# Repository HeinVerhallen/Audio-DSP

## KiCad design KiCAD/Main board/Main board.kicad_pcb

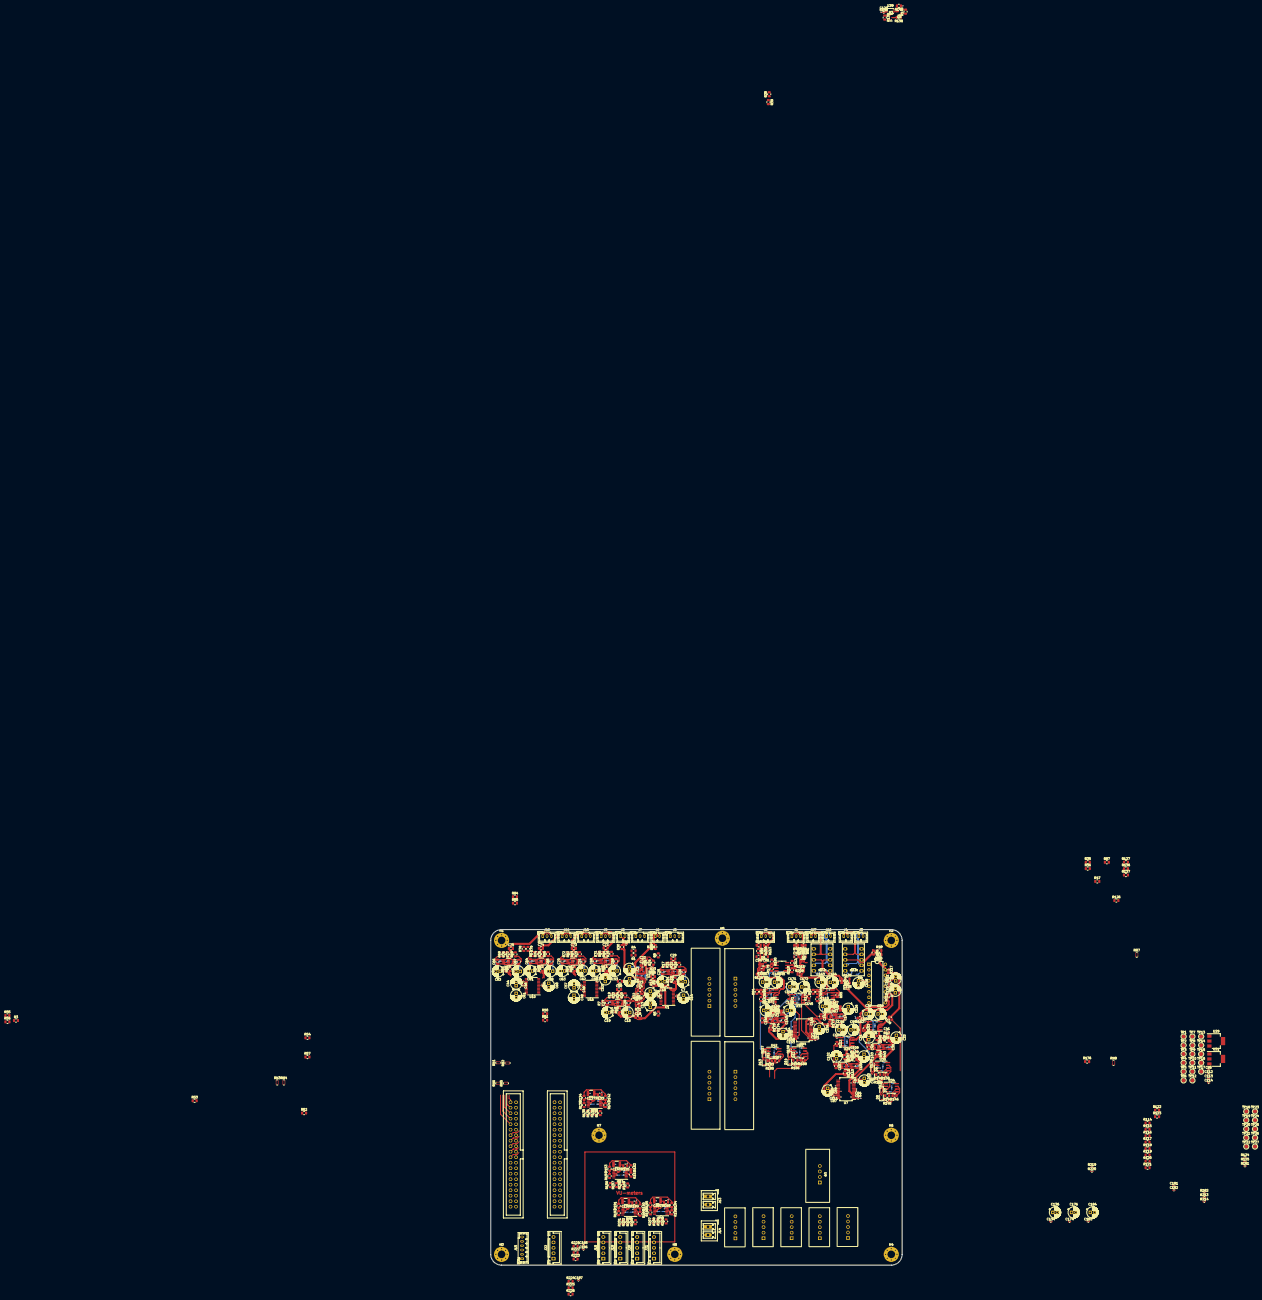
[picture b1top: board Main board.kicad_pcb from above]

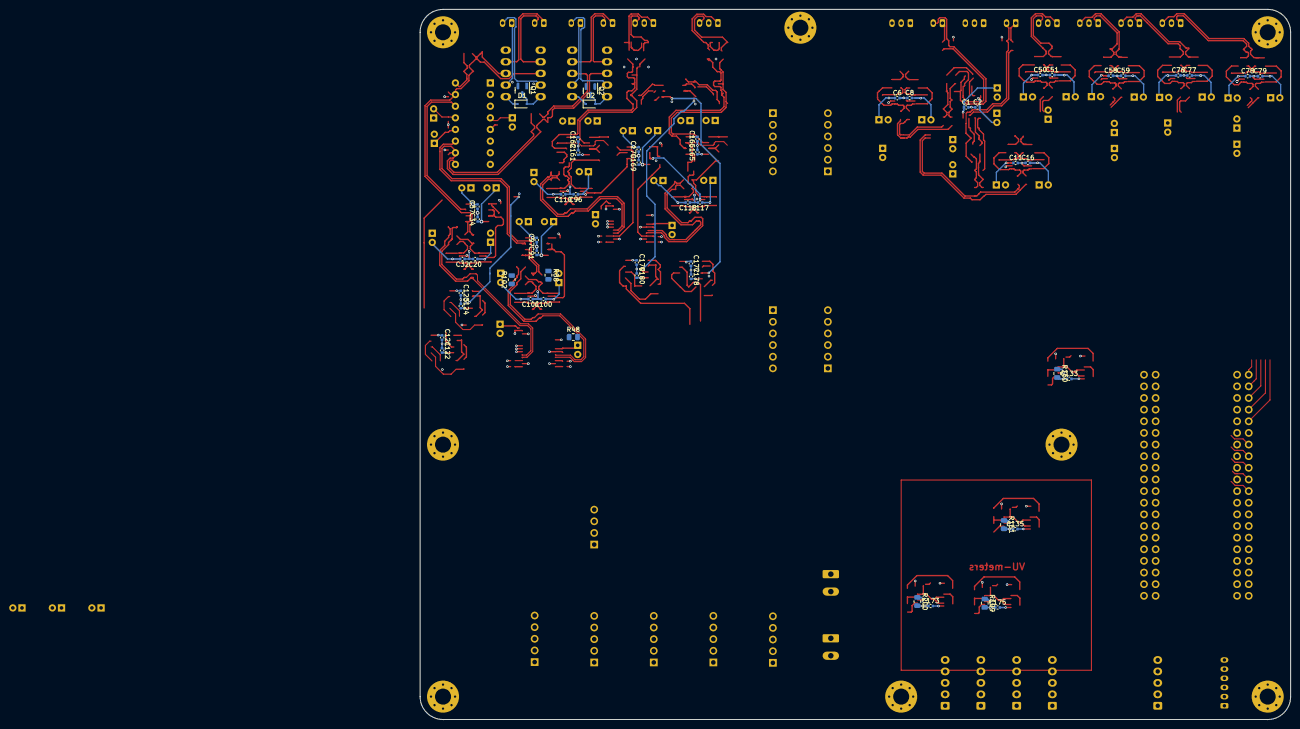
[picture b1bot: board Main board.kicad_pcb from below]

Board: 4 copper layers, 190.0 x 155.0 mm, 543 parts (55 on the bottom side), 359 nets.

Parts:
C1, C2, C5, C6, C8, C9, C11, C12, C16, C20, C32, C34, C37, C43, C45, C46, C47, C49, C50, C51, C52, C55, C58, C59, C76, C77, C78, C79, C84, C86, C87, C88, C91, C96, C97, C100, C101, C104, C109, C110, C111, C117, C118, C121, C122, C123, C124, C126, C127, C129, C130, C132, C133, C134, C135, C145, C146, C147, C148, C151, C153, C154, C155, C161, C162, C165, C166, C169, C170, C173, C174, C175, C177, C178, C179, C180, C181, C182, C183, C185, C186, C187: 100n; C_0402_1005Metric
C3, C4, C7, C10, C13, C14, C15, C19, C31, C33, C36, C38, C39, C42, C44, C48, C53, C54, C56, C57, C60, C61, C62, C63, C80, C81, C82, C83, C89, C98, C99, C102, C103, C115, C116, C119, C120, C125, C128, C131, C136, C152, C156, C163, C164, C167, C168, C171, C172, C176, C184: 22uF; CP_Radial_D5.0mm_P2.00mm
C17, C18: 4n7; C_0805_2012Metric
C21, C22, C23, C24: 1n5; C_0805_2012Metric
C25, C26, C27, C28, C64, C65, C66, C67, C68, C69, C70, C71: 680p; C_0805_2012Metric
C29, C30, C72, C73, C74, C75: 2n2; C_0805_2012Metric
C35, C40, C106, C107, C141, C142, C143, C144: 1n; C_0805_2012Metric
C41, C108, C149, C150: 2n7; C_0805_2012Metric
C85, C112, C113, C114: 1u; C_0402_1005Metric
C90, C92, C93, C94, C95, C105: 3n3; C_0805_2012Metric
C137, C140, C159, C160: 10u; C_1210_3225Metric
C138, C139, C157, C158: 47p; C_0402_1005Metric
D1, D2, D7, D8, D9, D10, D11, D12, D13, D14: 1N4148WS; D_SOD-323
D3, D4: STS321050B100; D_SOD-323
D5, D6: CPDT-12V; SOT-23
H1, H2, H3, H4, H5, H6, H7, H8: MountingHole_Pad; MountingHole_3.5mm_Pad_Via
J1, J2, J5, J7, J9, J10, J11, J12: Conn_01x03; JST_PH_B3B-PH-K_1x03_P2.00mm_Vertical
J3, J4, J6, J8, J16, J17: Conn_01x02; JST_PH_B2B-PH-K_1x02_P2.00mm_Vertical
J13, J14: Conn_01x02; PhoenixContact_MCV_1,5_2-G-3.81_1x02_P3.81mm_Vertical
J15: Conn_01x06; JST_PH_B6B-PH-K_1x06_P2.00mm_Vertical
J18, J19, J20, J21, J22: Conn_01x05; JST_XH_B5B-XH-A_1x05_P2.50mm_Vertical
K1, K2: EA2-12NU
Q1, Q2, Q3: BC847; SOT-23
Q4: BC857; SOT-23
R1, R2, R3, R4, R6, R7, R35, R36, R38, R39, R47, R48, R52, R53, R55, R56, R78, R79, R84, R85, R87, R88, R102, R114, R115, R116, R117, R118, R119, R120, R121, R122, R123, R136, R137, R176: 10R; R_0805_2012Metric
R5, R8, R50, R51, R54, R57: 4R7; R_0805_2012Metric
R9, R10, R13, R14: 10K; R_0805_2012Metric
R11, R12, R15, R16, R37, R40, R58, R59, R60, R61, R62, R63, R64, R65, R93, R94, R103, R106, R107, R112, R126, R127, R133, R134, R135, R147, R153, R154, R155, R163, R164, R165, R170, R171, R191, R192, R195, R196, R197, R198, R221, R222, R223, R224, R225, R226: 1k; R_0805_2012Metric
R17, R18, R19, R20, R66, R67, R68, R69, R70, R71, R72, R73: 4k7; R_0805_2012Metric
R21, R22, R23, R24: 820; R_0805_2012Metric
R25, R26, R27, R28: 4k3; R_0805_2012Metric
R29, R30: 22; R_0805_2012Metric
R31, R32, R33, R34, R43, R44, R74, R75, R76, R77, R80, R81, R82, R83, R110, R111, R172, R173, R174, R175: 39; R_0805_2012Metric
R41, R42, R108, R109: 2k7; R_0805_2012Metric
R45, R46, R86, R89, R90, R104: 47k; R_0805_2012Metric
R49, R91, R99, R101, R105, R113: 220; R_0805_2012Metric
R92, R100: 2M2; R_0805_2012Metric
R95, R96, R97, R98: 0; R_0805_2012Metric
R124, R125, R181, R182, R213, R214, R215, R216, R217, R218: 0R; R_0402_1005Metric
R128, R162: 100k; R_0805_2012Metric
R129, R130, R131, R132, R156, R157, R158, R159, R201, R202, R203, R204, R205, R206, R207, R208: 330; R_0805_2012Metric
R138, R139, R140, R141, R144, R145, R146, R148, R149, R150, R179, R180, R183, R184, R185, R186, R187, R188, R210, R212: 10k; R_0805_2012Metric
R142, R152, R190, R194: 2k; R_0805_2012Metric
R143, R151, R189, R193: 3k9; R_0805_2012Metric
R160, R161, R199, R200: 24k; R_0805_2012Metric
R166, R167, R168, R169: 270; R_0805_2012Metric
R177, R178, R209, R211: 150k; R_0805_2012Metric
R219, R220: 1k8; R_0402_1005Metric
RN1, RN2, RN3, RN4, RN5, RN6, RN7, RN8: 22R; R_Array_Convex_4x0402
TP1, TP2, TP3, TP4, TP5, TP6, TP7, TP8, TP9, TP10, TP11, TP12, TP13, TP14, TP15, TP16, TP17, TP18, TP19, TP20, TP21, TP22, TP23, TP24, TP25, TP26, TP27: TestPoint; TestPoint_Pad_D2.0mm
U1, U10, U16: PCM1789; TSSOP-24_4.4x7.8mm_P0.65mm
U2, U6, U24, U30, U32, U33: LM4562; SOIC-8_3.9x4.9mm_P1.27mm
U3, U4, U5, U11, U17, U22, U23, U25, U26, U27: OPA1632DR; VSSOP-8_3.0x3.0mm_P0.65_TP1.8x1.5
U7, U44: PCM1804; SSOP-28_5.3x10.2mm_P0.65mm
U8: DE1-SoC
U9: SEPIC_-15V_LT3579
U12, U13: LIN_REG_±5V; LIN_REG_±xxV
U14, U15: LIN_REG_±12V; LIN_REG_±xxV
U18, U28: 12V; BUCK_MAX17634C_xxV
U19: 5V; BUCK_MAX17634C_xxV
U20: 8V; BUCK_MAX17634C_xxV
U21: 15V; BUCK_MAX17634C_xxV
U29, U31: AP2111H-3.3TRG1; SOT-223
U34, U35, U42, U43, U45: TL072; SOIC-8_3.9x4.9mm_P1.27mm
U36, U37, U40, U41: LM339; TSSOP-14_4.4x5mm_P0.65mm
U38: PGA2311P; DIP-16_W7.62mm
U39: TXS0102; VSSOP-8_2.4x2.1mm_P0.5mm

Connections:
+3V3D1: C42.1, C43.2, C113.1, C130.2, C155.2, C156.1, R124.2, R125.2, R181.2, R182.2, R213.2, R214.2, TP2.1, U7.6 (FMT0), U7.14 (VDD), U7.19 (~RST), U29.2 (VOUT), U39.3 (VCCA), U44.6 (FMT0), U44.14 (VDD), U44.19 (~RST)
+3V3D2: C5.1, C39.1, C44.1, C45.1, C48.1, C49.1, C114.1, R219.1, R220.1, R221.1, R224.1, R225.1, TP10.1, U1.4 (RST), U1.6 (VDD), U10.4 (RST), U10.6 (VDD), U10.24 (ADR5/ADR1/RSV), U16.4 (RST), U16.6 (VDD), U16.23 (MS/ADR0/RSV), U31.2 (VOUT)
+5VA1: R48.1, R136.1, R176.1, TP3.1, U12.4 (+5V)
+5VA2: R5.1, R8.1, R50.1, R51.1, R54.1, R57.1, TP4.1, U13.4 (+5V)
+5VD1: C85.1, C112.1, C127.2, C128.1, C129.2, C133.1, C135.1, C173.1, C175.1, J15.3, J18.1, J19.1, J20.1, J21.1, Q4.2 (E), R140.2, R160.2, R161.2, R199.2, R200.2, TP1.1, U19.1 (VOUT), U19.2 (VOUT), U29.3 (VIN), U31.3 (VIN), U36.3 (V+), U37.3 (V+), U38.1 (ZCEN), U38.4 (VD+), U38.8 (~MUTE), U39.2 (VCCB), U40.3 (V+), U41.3 (V+)
+12VA1: R35.1, R38.1, R47.1, R88.1, R114.1, R116.1, R118.1, R120.1, R122.1, TP5.1, U14.4 (+12V)
+12VA2: R1.1, R3.1, R6.1, R52.1, R55.1, R78.1, R84.1, TP6.1, U15.4 (+12V)
+12VD1: D1.1 (K), D2.1 (K), K1.1, K2.1, TP13.1, U28.1 (VOUT), U28.2 (VOUT)
+15VD1: C121.1, C123.1, C177.1, C179.1, C181.1, TP11.1, U14.6 (+VIN), U15.6 (+VIN), U21.1 (VOUT), U21.2 (VOUT), U34.8 (V+), U35.8 (V+), U42.8 (V+), U43.8 (V+), U45.8 (V+)
-5VA1: R137.1, TP15.1, TP16.1, U12.3 (-5V), U13.3 (-5V)
-12VA1: R36.2, R39.2, R87.2, R102.2, R115.2, R117.2, R119.2, R121.2, R123.2, TP7.1, U14.3 (-12V)
-12VA2: R2.2, R4.2, R7.2, R53.2, R56.2, R79.2, R85.2, TP8.1, U15.3 (-12V)
-15VD1: C122.2, C124.2, C178.2, C180.2, C182.2, TP17.1, U9.3 (VOUT), U12.1 (-VIN), U13.1 (-VIN), U14.1 (-VIN), U15.1 (-VIN), U34.4 (V-), U35.4 (V-), U42.4 (V-), U43.4 (V-), U45.4 (V-)
/ADC_CH1_2/AGND_CH1: C90.2, D3.1 (A1), K1.8, R40.1, R86.2, R217.1, U38.15 (AGNDL)
/ADC_CH1_2/AGND_CH2: C105.2, D4.1 (A1), K2.8, R104.2, R107.1, R218.1, U38.10 (AGNDR)
/ADC_CH1_2/BCK_ADC_CH1_2: RN7.6 (R3.2), U8.9(GPIO_0) (GPIO_0_D8)
/ADC_CH1_2/DATA_ADC_CH1_2: RN7.5 (R4.2), U8.13(GPIO_0) (GPIO_0_D10)
/ADC_CH1_2/INPUT_SELECTOR_RELAY_CH1: R126.2, U8.1(GPIO_0) (GPIO_0_D0)
/ADC_CH1_2/INPUT_SELECTOR_RELAY_CH2: R127.2, U8.3(GPIO_0) (GPIO_0_D2)
/ADC_CH1_2/JACK_CH1(+): J4.1, K1.4
/ADC_CH1_2/JACK_CH1(REF): J4.2, K1.7
/ADC_CH1_2/JACK_CH2(+): J17.1, K2.4
/ADC_CH1_2/JACK_CH2(REF): J17.2, K2.7
/ADC_CH1_2/LRCK_ADC_CH1_2: RN7.7 (R2.2), U8.7(GPIO_0) (GPIO_0_D6)
/ADC_CH1_2/RCA_CH1(+): J3.1, K1.2
/ADC_CH1_2/RCA_CH1(REF): J3.2, K1.9
/ADC_CH1_2/RCA_CH2(+): J16.1, K2.2
/ADC_CH1_2/RCA_CH2(REF): J16.2, K2.9
/ADC_CH1_2/SCKI_ADC_CH1_2: RN7.8 (R1.2), U8.5(GPIO_0) (GPIO_0_D4)
/ADC_CH1_2/TXS0102_SCLK_CH1_2: U8.23(GPIO_0) (GPIO_0_D20), U39.5 (A1)
/ADC_CH1_2/TXS0102_SDA_CH1_2: U8.25(GPIO_0) (GPIO_0_D22), U39.4 (A2)
/ADC_CH1_2/VU_G1_CH1: J18.2, R129.1
/ADC_CH1_2/VU_G1_CH2: J19.2, R156.1
/ADC_CH1_2/VU_G2_CH1: J18.3, R130.1
/ADC_CH1_2/VU_G2_CH2: J19.3, R157.1
/ADC_CH1_2/VU_O1_CH1: J18.4, R131.1
/ADC_CH1_2/VU_O1_CH2: J19.4, R158.1
/ADC_CH1_2/VU_R1_CH1: J18.5, R132.1
/ADC_CH1_2/VU_R1_CH2: J19.5, R159.1
/ADC_CH1_2/~TXS0102_OE_CH1_2: R139.2, U8.27(GPIO_0) (GPIO_0_D24)
/ADC_CH3_4/BCK_ADC_CH3_4: RN8.6 (R3.2), U8.19(GPIO_0) (GPIO_0_D16)
/ADC_CH3_4/DATA_ADC_CH3_4: RN8.5 (R4.2), U8.21(GPIO_0) (GPIO_0_D18)
/ADC_CH3_4/LRCK_ADC_CH3_4: RN8.7 (R2.2), U8.17(GPIO_0) (GPIO_0_D14)
/ADC_CH3_4/SCKI_ADC_CH3_4: RN8.8 (R1.2), U8.15(GPIO_0) (GPIO_0_D12)
/ADC_CH3_4/VU_G1_CH3: J20.2, R201.1
/ADC_CH3_4/VU_G1_CH4: J21.2, R205.1
/ADC_CH3_4/VU_G2_CH3: J20.3, R202.1
/ADC_CH3_4/VU_G2_CH4: J21.3, R206.1
/ADC_CH3_4/VU_O1_CH3: J20.4, R203.1
/ADC_CH3_4/VU_O1_CH4: J21.4, R207.1
/ADC_CH3_4/VU_R1_CH3: J20.5, R204.1
/ADC_CH3_4/VU_R1_CH4: J21.5, R208.1
/ADC_CH3_4/XLR_CH3(+): J1.1, R89.1, R91.1
/ADC_CH3_4/XLR_CH3(-): J1.3, R90.2, R101.1
/ADC_CH3_4/XLR_CH4(+): J2.1, R46.2, R113.1
/ADC_CH3_4/XLR_CH4(-): J2.3, R45.1, R99.1
/DAC_CH1_2/AMUTEI_DAC_CH1_2: RN2.1 (R1.1), U8.33(GPIO_1) (GPIO_1_D28)
/DAC_CH1_2/BCK_DAC_CH1_2: RN1.2 (R2.1), U8.27(GPIO_1) (GPIO_1_D24)
/DAC_CH1_2/DIN_DAC_CH1_2: RN1.3 (R3.1), U8.25(GPIO_1) (GPIO_1_D22)
/DAC_CH1_2/I2C_SCL_DAC: R219.2, RN2.3 (R3.1), RN4.3 (R3.1), RN6.3 (R3.1), U8.35(GPIO_1) (GPIO_1_D30)
/DAC_CH1_2/I2C_SDA_DAC: R220.2, RN2.2 (R2.1), RN4.2 (R2.1), RN6.2 (R2.1), U8.37(GPIO_1) (GPIO_1_D32)
/DAC_CH1_2/LRCK_DAC_CH1_2: RN1.1 (R1.1), U8.31(GPIO_1) (GPIO_1_D26)
/DAC_CH1_2/RCA_JACK_CH1(+): J6.1, R29.2
/DAC_CH1_2/RCA_JACK_CH1(REF): C22.2, J6.2, R26.2, R216.1
/DAC_CH1_2/RCA_JACK_CH2(+): J8.1, R30.2
/DAC_CH1_2/RCA_JACK_CH2(REF): C24.2, J8.2, R28.2, R215.1
/DAC_CH1_2/SCKI_DAC_CH1_2: RN1.4 (R4.1), U8.23(GPIO_1) (GPIO_1_D20)
/DAC_CH1_2/VOUT_XLR_CH1(+): C29.2, J5.1, R18.2, R32.2
/DAC_CH1_2/VOUT_XLR_CH1(-): C29.1, J5.3, R17.2, R31.2
/DAC_CH1_2/VOUT_XLR_CH2(+): C30.2, J7.1, R20.2, R34.2
/DAC_CH1_2/VOUT_XLR_CH2(-): C30.1, J7.3, R19.2, R33.2
/DAC_CH3_4/AMUTEI_DAC_CH3_4: RN4.1 (R1.1), U8.21(GPIO_1) (GPIO_1_D18)
/DAC_CH3_4/BCK_DAC_CH3_4: RN3.2 (R2.1), U8.17(GPIO_1) (GPIO_1_D14)
/DAC_CH3_4/DIN_DAC_CH3_4: RN3.3 (R3.1), U8.15(GPIO_1) (GPIO_1_D12)
/DAC_CH3_4/LRCK_DAC_CH3_4: RN3.1 (R1.1), U8.19(GPIO_1) (GPIO_1_D16)
/DAC_CH3_4/SCKI_DAC_CH3_4: RN3.4 (R4.1), U8.13(GPIO_1) (GPIO_1_D10)
/DAC_CH3_4/VOUT_XLR_CH3(+): C72.2, J9.1, R70.2, R81.2
/DAC_CH3_4/VOUT_XLR_CH3(-): C72.1, J9.3, R71.2, R80.2
/DAC_CH3_4/VOUT_XLR_CH4(+): C73.2, J10.1, R73.2, R83.2
/DAC_CH3_4/VOUT_XLR_CH4(-): C73.1, J10.3, R72.2, R82.2
/DAC_CH5_6/AMUTEI_DAC_CH5_6: RN6.1 (R1.1), U8.9(GPIO_1) (GPIO_1_D8)
/DAC_CH5_6/BCK_DAC_CH5_6: RN5.2 (R2.1), U8.5(GPIO_1) (GPIO_1_D4)
/DAC_CH5_6/DIN_DAC_CH5_6: RN5.3 (R3.1), U8.3(GPIO_1) (GPIO_1_D2)
/DAC_CH5_6/LRCK_DAC_CH5_6: RN5.1 (R1.1), U8.7(GPIO_1) (GPIO_1_D6)
/DAC_CH5_6/SCKI_DAC_CH5_6: RN5.4 (R4.1), U8.1(GPIO_1) (GPIO_1_D0)
/DAC_CH5_6/VOUT_XLR_CH5(+): C74.2, J11.1, R66.2, R75.2
/DAC_CH5_6/VOUT_XLR_CH5(-): C74.1, J11.3, R67.2, R74.2
/DAC_CH5_6/VOUT_XLR_CH6(+): C75.2, J12.1, R69.2, R77.2
/DAC_CH5_6/VOUT_XLR_CH6(-): C75.1, J12.3, R68.2, R76.2
/FPGA/ENC_A: C187.1, R226.1, U8.31(GPIO_0) (GPIO_0_D26)
/FPGA/ENC_B: C186.1, R222.1, U8.33(GPIO_0) (GPIO_0_D28)
/FPGA/ENC_SW: C185.1, R223.1, U8.35(GPIO_0) (GPIO_0_D30)
/FPGA/UI_RX: J15.6, U8.37(GPIO_0) (GPIO_0_D32)
/FPGA/UI_TX: J15.4, U8.39(GPIO_0) (GPIO_0_D34)
/POWER_SUPPLIES/DC_POWER_IN: J13.1, TP14.1, U18.5 (VIN), U19.5 (VIN), U20.5 (VIN), U21.5 (VIN), U28.5 (VIN)
GND: C1.2, C2.1, C3.2, C4.1, C5.2, C6.2, C7.2, C8.1, C9.2, C10.1, C11.2, C12.2, C13.2, C14.2, C15.2, C16.1, C19.1, C20.2, C31.2, C32.1, C33.1, C34.2, C36.2, C37.1, C38.1, C39.2, C42.2, C43.1, C44.2, C45.2, C46.2, C47.2, C48.2, C49.2, C50.2, C51.1, C52.2, C53.2, C54.1, C55.2, C56.2, C57.2, C58.2, C59.1, C60.2, C61.2, C62.2, C63.1, C76.2, C77.1, C78.2, C79.1, C80.2, C81.1, C82.2, C83.1, C84.2, C85.2, C86.2, C87.2, C88.1, C89.2, C91.2, C92.2, C93.1, C94.2, C95.1, C96.2, C97.1, C98.2, C99.1, C100.2, C101.1, C102.2, C103.1, C104.1, C109.1, C110.1, C111.2, C112.2, C113.2, C114.2, C115.2, C116.1, C117.2, C118.1, C119.2, C120.1, C121.2, C122.1, C123.2, C124.1, C125.2, C126.1, C127.1, C128.2, C129.1, C130.1, C131.1, C132.1, C133.2, C134.2, C135.2, C136.2, C137.2, C140.2, C145.1, C146.1, C147.2, C148.2, C151.2, C152.2, C153.2, C154.1, C155.1, C156.2, C159.2, C160.2, C161.2, C162.1, C163.2, C164.1, C165.2, C166.1, C167.2, C168.1, C169.2, C170.1, C171.2, C172.1, C173.2, C174.2, C175.2, C176.2, C177.2, C178.1, C179.2, C180.1, C181.2, C182.1, C183.2, C184.2, C185.2, C186.2, C187.2, H1.1, H2.1, H3.1, H4.1, H5.1, H6.1, H7.1, H8.1, J1.2, J2.2, J5.2, J7.2, J9.2, J10.2, J11.2, J12.2, J13.2, J14.2, J15.1, J22.4, J22.5, Q1.2 (E), Q2.2 (E), Q3.2 (E), R92.2, R100.2, R133.1, R135.1, R141.1, R145.1, R149.1, R154.1, R155.1, R180.1, R185.1, R186.1, R192.1, R196.1, R197.1, R198.1, R212.1, R215.2, R216.2, R217.2, R218.2, TP18.1, TP19.1, TP20.1, TP21.1, TP22.1, TP23.1, TP24.1, TP25.1, TP26.1, TP27.1, U1.7 (DGND), U1.10 (AGND1), U1.15 (AGND2), U1.20 (MODE), U1.23 (MS/ADR0/RSV), U1.24 (ADR5/ADR1/RSV), U3.2 (VOCM), U3.7 (ENABLE), U3.9 (GND), U4.2 (VOCM), U4.7 (ENABLE), U4.9 (GND), U5.7 (ENABLE), U5.9 (GND), U7.2 (AGNDL), U7.7 (FMT1), U7.8 (S/~M), U7.12 (BYPAS), U7.13 (DGND), U7.23 (AGND), U7.27 (AGNDR), U8.2(GPIO_0) (GPIO_0_D1), U8.2(GPIO_1) (GPIO_1_D1), U8.4(GPIO_0) (GPIO_0_D3), U8.4(GPIO_1) (GPIO_1_D3), U8.6(GPIO_0) (GPIO_0_D5), U8.6(GPIO_1) (GPIO_1_D5), U8.8(GPIO_0) (GPIO_0_D7), U8.8(GPIO_1) (GPIO_1_D7), U8.10(GPIO_0) (GPIO_0_D9), U8.10(GPIO_1) (GPIO_1_D9), U8.12(GPIO_0) (GND), U8.12(GPIO_1) (GND), U8.14(GPIO_0) (GPIO_0_D11), U8.14(GPIO_1) (GPIO_1_D11), U8.16(GPIO_0) (GPIO_0_D13), U8.16(GPIO_1) (GPIO_1_D13), U8.18(GPIO_0) (GPIO_0_D15), U8.18(GPIO_1) (GPIO_1_D15), U8.20(GPIO_0) (GPIO_0_D17), U8.20(GPIO_1) (GPIO_1_D17), U8.22(GPIO_0) (GPIO_0_D19), U8.22(GPIO_1) (GPIO_1_D19), U8.24(GPIO_0) (GPIO_0_D21), U8.24(GPIO_1) (GPIO_1_D21), U8.26(GPIO_0) (GPIO_0_D23), U8.26(GPIO_1) (GPIO_1_D23), U8.28(GPIO_0) (GPIO_0_D25), U8.28(GPIO_1) (GPIO_1_D25), U8.30(GPIO_0) (GND), U8.30(GPIO_1) (GND), U8.32(GPIO_0) (GPIO_0_D27), U8.32(GPIO_1) (GPIO_1_D27), U8.34(GPIO_0) (GPIO_0_D29), U8.34(GPIO_1) (GPIO_1_D29), U8.36(GPIO_0) (GPIO_0_D31), U8.36(GPIO_1) (GPIO_1_D31), U8.38(GPIO_0) (GPIO_0_D33), U8.38(GPIO_1) (GPIO_1_D33), U8.40(GPIO_0) (GPIO_0_D35), U8.40(GPIO_1) (GPIO_1_D35), U9.2 (GND), U9.4 (GND), U10.7 (DGND), U10.10 (AGND1), U10.15 (AGND2), U10.20 (MODE), U10.23 (MS/ADR0/RSV), U11.2 (VOCM), U11.7 (ENABLE), U11.9 (GND), U12.2 (GND), U12.5 (GND), U13.2 (GND)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
unnamed: C17.1, R9.1, R23.1, R25.1
unnamed: C17.2, R10.2, R24.1, R26.1
unnamed: C18.1, R13.1, R21.1, R27.1
unnamed: C18.2, R14.2, R22.1, R28.1
unnamed: C21.2, R25.2, R29.1, U2.1
unnamed: C23.2, R27.2, R30.1, U2.7
unnamed: D1.2 (A), K1.10, Q1.3 (C)
unnamed: D2.2 (A), K2.10, Q2.3 (C)
unnamed: C90.1, D3.2 (A2), R49.2, U38.16 (VINL)
unnamed: C105.1, D4.2 (A2), R105.2, U38.9 (VINR)
unnamed: C93.2, D5.1 (A1), R101.2, R211.2, U30.6 (-)
unnamed: C92.1, D5.2 (A2), R91.2, R209.2, U30.2 (-)
unnamed: C95.2, D6.1 (A1), R113.2, R177.2, U32.2 (-)
unnamed: C94.1, D6.2 (A2), R99.2, R178.2, U32.6 (-)
unnamed: C138.1, D7.2 (A), R144.2, U34.2 (-)
unnamed: C138.2, D7.1 (K), D8.2 (A), U34.1
unnamed: D8.1 (K), R145.2, U34.5 (+)
unnamed: C139.1, D9.2 (A), R148.2, U35.2 (-)
unnamed: C139.2, D9.1 (K), D10.2 (A), U35.1
unnamed: D10.1 (K), R149.2, U35.5 (+)
unnamed: C157.1, D11.2 (A), R183.2, U42.2 (-)
unnamed: C157.2, D11.1 (K), D13.2 (A), U42.1
unnamed: C158.1, D12.2 (A), R184.2, U43.2 (-)
unnamed: C158.2, D12.1 (K), D14.2 (A), U43.1
unnamed: D13.1 (K), R185.2, U42.5 (+)
unnamed: D14.1 (K), R186.2, U43.5 (+)
unnamed: J22.1, R221.2, R226.2
unnamed: J22.2, R222.2, R224.2
unnamed: J22.3, R223.2, R225.2
unnamed: K1.3, R49.1, R86.1
unnamed: K2.3, R104.1, R105.1
unnamed: Q1.1 (B), R126.1
unnamed: Q2.1 (B), R127.1
unnamed: Q3.1 (B), R139.1
unnamed: Q3.3 (C), R138.2
unnamed: Q4.1 (B), R138.1, R140.1
unnamed: Q4.3 (C), R141.2, U39.6 (OE)
unnamed: R89.2, R90.1, R92.1
unnamed: R45.2, R46.1, R100.1
unnamed: R129.2, U36.2
unnamed: R130.2, U36.1
unnamed: R131.2, U36.13
unnamed: R132.2, U36.14
unnamed: R96.2, R147.1, U30.7
unnamed: R156.2, U37.2
unnamed: R157.2, U37.1
unnamed: R158.2, U37.13
unnamed: R159.2, U37.14
unnamed: R98.2, R163.1, U32.7
unnamed: R95.2, R164.1, U30.1
unnamed: R97.2, R165.1, U32.1
unnamed: R201.2, U40.2
unnamed: R202.2, U40.1
unnamed: R203.2, U40.13
unnamed: R204.2, U40.14
unnamed: R205.2, U41.2
unnamed: R206.2, U41.1
unnamed: R207.2, U41.13
unnamed: R208.2, U41.14
unnamed: RN1.8 (R1.2), U1.1 (LRCK)
unnamed: RN1.7 (R2.2), U1.2 (BCK)
unnamed: RN1.6 (R3.2), U1.3 (DIN)
unnamed: RN1.5 (R4.2), U1.5 (SCKI)
unnamed: RN2.8 (R1.2), U1.17 (AMUTEI)
unnamed: RN2.7 (R2.2), U1.21 (MD/SDA/DEMP)
unnamed: RN2.6 (R3.2), U1.22 (MC/SCL/FMT)
unnamed: RN3.8 (R1.2), U16.1 (LRCK)
unnamed: RN3.7 (R2.2), U16.2 (BCK)
unnamed: RN3.6 (R3.2), U16.3 (DIN)
unnamed: RN3.5 (R4.2), U16.5 (SCKI)
unnamed: RN4.8 (R1.2), U16.17 (AMUTEI)
unnamed: RN4.7 (R2.2), U16.21 (MD/SDA/DEMP)
unnamed: RN4.6 (R3.2), U16.22 (MC/SCL/FMT)
unnamed: RN5.8 (R1.2), U10.1 (LRCK)
unnamed: RN5.7 (R2.2), U10.2 (BCK)
unnamed: RN5.6 (R3.2), U10.3 (DIN)
unnamed: RN5.5 (R4.2), U10.5 (SCKI)
unnamed: RN6.8 (R1.2), U10.17 (AMUTEI)
unnamed: RN6.7 (R2.2), U10.21 (MD/SDA/DEMP)
unnamed: RN6.6 (R3.2), U10.22 (MC/SCL/FMT)
unnamed: RN7.1 (R1.1), U7.18 (SCKI)
unnamed: RN7.2 (R2.1), U7.17 (LRCK/DSDBCK)
unnamed: RN7.3 (R3.1), U7.16 (BCK/DSDL)
unnamed: RN7.4 (R4.1), U7.15 (DATA/DSDR)
unnamed: RN8.1 (R1.1), U44.18 (SCKI)
unnamed: RN8.2 (R2.1), U44.17 (LRCK/DSDBCK)
unnamed: RN8.3 (R3.1), U44.16 (BCK/DSDL)
unnamed: RN8.4 (R4.1), U44.15 (DATA/DSDR)
unnamed: C9.1, C13.1, R5.2, U1.8 (VCC1)
unnamed: C12.1, C14.1, R8.2, U1.16 (VCC2)
unnamed: C134.1, C136.1, U1.9 (VCOM)
unnamed: R10.1, R11.1, U1.12 (VOUTL+)
unnamed: R9.2, R12.1, U1.11 (VOUTL-)
unnamed: R14.1, R15.1, U1.13 (VOUTR+)
unnamed: R13.2, R16.1, U1.14 (VOUTR-)
unnamed: C21.1, R23.2, U2.3 (+)
unnamed: C22.1, R24.2, U2.2 (-)
unnamed: C23.1, R21.2, U2.5 (+)
unnamed: C24.1, R22.2, U2.6 (-)
unnamed: C1.1, C3.1, R1.2, U2.8 (V+)
unnamed: C2.2, C4.2, R2.1, U2.4 (V-)
unnamed: C25.1, R11.2, R17.1, U3.8 (VIN+)
unnamed: C26.1, R12.2, R18.1, U3.1 (VIN-)
unnamed: C26.2, R32.1, U3.4 (VOUT+)
unnamed: C25.2, R31.1, U3.5 (VOUT-)
unnamed: C6.1, C7.1, R3.2, U3.3 (V+)
unnamed: C8.2, C10.2, R4.1, U3.6 (V-)
unnamed: C27.1, R15.2, R19.1, U4.8 (VIN+)
unnamed: C28.1, R16.2, R20.1, U4.1 (VIN-)
unnamed: C28.2, R34.1, U4.4 (VOUT+)
unnamed: C27.2, R33.1, U4.5 (VOUT-)
unnamed: C11.1, C15.1, R6.2, U4.3 (V+)
unnamed: C16.2, C19.2, R7.1, U4.6 (V-)
unnamed: C35.1, R37.2, R41.1, U5.8 (VIN+)
unnamed: C40.1, R40.2, R42.1, U5.1 (VIN-)
unnamed: U5.2 (VOCM), U6.6 (-), U6.7
unnamed: C40.2, R44.1, U5.4 (VOUT+)
unnamed: C35.2, R43.1, U5.5 (VOUT-)
unnamed: C20.1, C31.1, R35.2, U5.3 (V+)
unnamed: C32.2, C33.2, R36.1, U5.6 (V-)
unnamed: R37.1, U6.1, U6.2 (-)
unnamed: C104.2, R103.1, U6.5 (+)
unnamed: C34.1, C36.1, R38.2, U6.8 (V+)
unnamed: C37.2, C38.2, R39.1, U6.4 (V-)
unnamed: R124.1, U7.9 (OSR0)
unnamed: R125.1, U7.10 (OSR1)
unnamed: R181.1, U7.11 (OSR2)
unnamed: C88.2, C89.1, R48.2, U7.22 (VCC)
unnamed: C84.1, R103.2, U7.3 (VCOML)
unnamed: C111.1, R112.2, U7.26 (VCOMR)
unnamed: C41.1, R41.2, R43.2, U7.4 (VINL+)
unnamed: C41.2, R42.2, R44.2, U7.5 (VINL-)
unnamed: C108.1, R108.2, R110.2, U7.25 (VINR+)
unnamed: C108.2, R109.2, R111.2, U7.24 (VINR-)
unnamed: C86.1, U7.1 (VREFL)
unnamed: C87.1, U7.28 (VREFR)
unnamed: TP12.1, U9.1 (VIN), U18.1 (VOUT), U18.2 (VOUT)
unnamed: C46.1, C60.1, R50.2, U10.8 (VCC1)
unnamed: C47.1, C61.1, R51.2, U10.16 (VCC2)
unnamed: C183.1, C184.1, U10.9 (VCOM)
unnamed: R59.1, U10.12 (VOUTL+)
unnamed: R58.1, U10.11 (VOUTL-)
unnamed: R62.1, U10.13 (VOUTR+)
unnamed: R63.1, U10.14 (VOUTR-)
unnamed: C68.1, R60.2, R71.1, U11.8 (VIN+)
unnamed: C69.1, R61.2, R70.1, U11.1 (VIN-)
unnamed: C69.2, R81.1, U11.4 (VOUT+)
unnamed: C68.2, R80.1, U11.5 (VOUT-)
unnamed: C50.1, C53.1, R52.2, U11.3 (V+)
unnamed: C51.2, C54.2, R53.1, U11.6 (V-)
unnamed: TP9.1, U12.6 (+VIN), U13.6 (+VIN), U20.1 (VOUT), U20.2 (VOUT)
unnamed: C52.1, C56.1, R54.2, U16.8 (VCC1)
unnamed: C55.1, C57.1, R57.2, U16.16 (VCC2)
unnamed: C174.1, C176.1, U16.9 (VCOM)
unnamed: R61.1, U16.12 (VOUTL+)
unnamed: R60.1, U16.11 (VOUTL-)
unnamed: R64.1, U16.13 (VOUTR+)
unnamed: R65.1, U16.14 (VOUTR-)
unnamed: C70.1, R64.2, R72.1, U17.8 (VIN+)
unnamed: C71.1, R65.2, R73.1, U17.1 (VIN-)
unnamed: C71.2, R83.1, U17.4 (VOUT+)
unnamed: C70.2, R82.1, U17.5 (VOUT-)
unnamed: C58.1, C62.1, R55.2, U17.3 (V+)
unnamed: C59.2, C63.2, R56.1, U17.6 (V-)
unnamed: C64.1, R58.2, R67.1, U22.8 (VIN+)
unnamed: C65.1, R59.2, R66.1, U22.1 (VIN-)
unnamed: C65.2, R75.1, U22.4 (VOUT+)
unnamed: C64.2, R74.1, U22.5 (VOUT-)
unnamed: C76.1, C80.1, R78.2, U22.3 (V+)
unnamed: C77.2, C81.2, R79.1, U22.6 (V-)
unnamed: C66.1, R62.2, R68.1, U23.8 (VIN+)
unnamed: C67.1, R63.2, R69.1, U23.1 (VIN-)
unnamed: C67.2, R77.1, U23.4 (VOUT+)
unnamed: C66.2, R76.1, U23.5 (VOUT-)
unnamed: C78.1, C82.1, R84.2, U23.3 (V+)
unnamed: C79.2, C83.2, R85.1, U23.6 (V-)
unnamed: R162.1, U24.3 (+), U38.11 (VOUTR)
unnamed: R106.1, U24.1, U24.2 (-)
unnamed: C109.2, R112.1, U24.5 (+)
unnamed: U24.6 (-), U24.7, U25.2 (VOCM)
unnamed: C91.1, C98.1, R47.2, U24.8 (V+)
unnamed: C97.2, C99.2, R87.1, U24.4 (V-)
unnamed: C106.1, R106.2, R108.1, U25.8 (VIN+)
unnamed: C107.1, R107.2, R109.1, U25.1 (VIN-)
unnamed: C107.2, R111.1, U25.4 (VOUT+)
unnamed: C106.2, R110.1, U25.5 (VOUT-)
unnamed: C100.1, C102.1, R88.2, U25.3 (V+)
unnamed: C101.2, C103.2, R102.1, U25.6 (V-)
unnamed: C141.1, R164.2, R166.1, U26.8 (VIN+)
unnamed: C142.1, R147.2, R167.1, U26.1 (VIN-)
unnamed: U26.2 (VOCM), U33.1, U33.2 (-)
unnamed: C142.2, R173.1, U26.4 (VOUT+)
unnamed: C141.2, R172.1, U26.5 (VOUT-)
unnamed: C96.1, C115.1, R114.2, U26.3 (V+)
unnamed: C110.2, C116.2, R115.1, U26.6 (V-)
unnamed: C143.1, R165.2, R168.1, U27.8 (VIN+)
unnamed: C144.1, R163.2, R169.1, U27.1 (VIN-)
unnamed: U27.2 (VOCM), U33.6 (-), U33.7
unnamed: C144.2, R175.1, U27.4 (VOUT+)
unnamed: C143.2, R174.1, U27.5 (VOUT-)
unnamed: C117.1, C119.1, R116.2, U27.3 (V+)
unnamed: C118.2, C120.2, R117.1, U27.6 (V-)
unnamed: R93.1, R95.1, U30.3 (+)
unnamed: R93.2, R96.1, U30.5 (+)
unnamed: C161.1, C163.1, R118.2, U30.8 (V+)
unnamed: C162.2, C164.2, R119.1, U30.4 (V-)
unnamed: R94.1, R97.1, U32.3 (+)
unnamed: R94.2, R98.1, U32.5 (+)
unnamed: C165.1, C167.1, R120.2, U32.8 (V+)
unnamed: C166.2, C168.2, R121.1, U32.4 (V-)
unnamed: C145.2, R170.1, U33.3 (+)
unnamed: C146.2, R171.1, U33.5 (+)
unnamed: C169.1, C171.1, R122.2, U33.8 (V+)
unnamed: C170.2, C172.2, R123.1, U33.4 (V-)
unnamed: R128.1, U34.3 (+)
unnamed: R144.1, R146.2, U34.6 (-)
unnamed: R162.2, U35.3 (+)
unnamed: R148.1, R150.2, U35.6 (-)
unnamed: C137.1, R133.2, R160.1, U36.5 (+), U36.7 (+), U36.9 (+), U36.11 (+)
unnamed: R143.2, R146.1, U34.7, U36.4 (-)
unnamed: R142.2, R143.1, U36.6 (-)
unnamed: R134.2, R142.1, U36.10 (-)
unnamed: R134.1, R135.2, U36.8 (-)
unnamed: C140.1, R155.2, R161.1, U37.5 (+), U37.7 (+), U37.9 (+), U37.11 (+)
unnamed: R150.1, R151.2, U35.7, U37.4 (-)
unnamed: R151.1, R152.2, U37.6 (-)
unnamed: R152.1, R153.2, U37.10 (-)
unnamed: R153.1, R154.2, U37.8 (-)
unnamed: U38.6 (SCLK), U39.8 (B1)
unnamed: U38.3 (SDI), U39.1 (B2)
unnamed: C125.1, C126.2, R136.2, U38.12 (VA+)
unnamed: C131.2, C132.2, R137.2, U38.13 (VA-)
unnamed: R128.2, U6.3 (+), U38.14 (VOUTL)
unnamed: C159.1, R197.2, R199.1, U40.5 (+), U40.7 (+), U40.9 (+), U40.11 (+)
unnamed: R187.1, R189.2, U40.4 (-), U42.7
unnamed: R189.1, R190.2, U40.6 (-)
unnamed: R190.1, R191.2, U40.10 (-)
unnamed: R191.1, R192.2, U40.8 (-)
unnamed: C160.1, R198.2, R200.1, U41.5 (+), U41.7 (+), U41.9 (+), U41.11 (+)
unnamed: R188.1, R193.2, U41.4 (-), U43.7
unnamed: R193.1, R194.2, U41.6 (-)
unnamed: R194.1, R195.2, U41.10 (-)
unnamed: R195.1, R196.2, U41.8 (-)
unnamed: R210.1, U42.3 (+), U45.1
unnamed: R183.1, R187.2, U42.6 (-)
unnamed: R179.1, U43.3 (+), U45.7
unnamed: R184.1, R188.2, U43.6 (-)
unnamed: R182.1, U44.9 (OSR0)
unnamed: R213.1, U44.10 (OSR1)
unnamed: R214.1, U44.11 (OSR2)
unnamed: C152.1, C154.2, R176.2, U44.22 (VCC)
unnamed: C147.1, R170.2, U44.3 (VCOML)
unnamed: C148.1, R171.2, U44.26 (VCOMR)
unnamed: C149.1, R166.2, R172.2, U44.4 (VINL+)
unnamed: C149.2, R167.2, R173.2, U44.5 (VINL-)
unnamed: C150.1, R168.2, R174.2, U44.25 (VINR+)
unnamed: C150.2, R169.2, R175.2, U44.24 (VINR-)
unnamed: C151.1, U44.1 (VREFL)
unnamed: C153.1, U44.28 (VREFR)
unnamed: R211.1, R212.2, U45.3 (+)
unnamed: R209.1, R210.2, U45.2 (-)
unnamed: R178.1, R180.2, U45.5 (+)
unnamed: R177.1, R179.2, U45.6 (-)

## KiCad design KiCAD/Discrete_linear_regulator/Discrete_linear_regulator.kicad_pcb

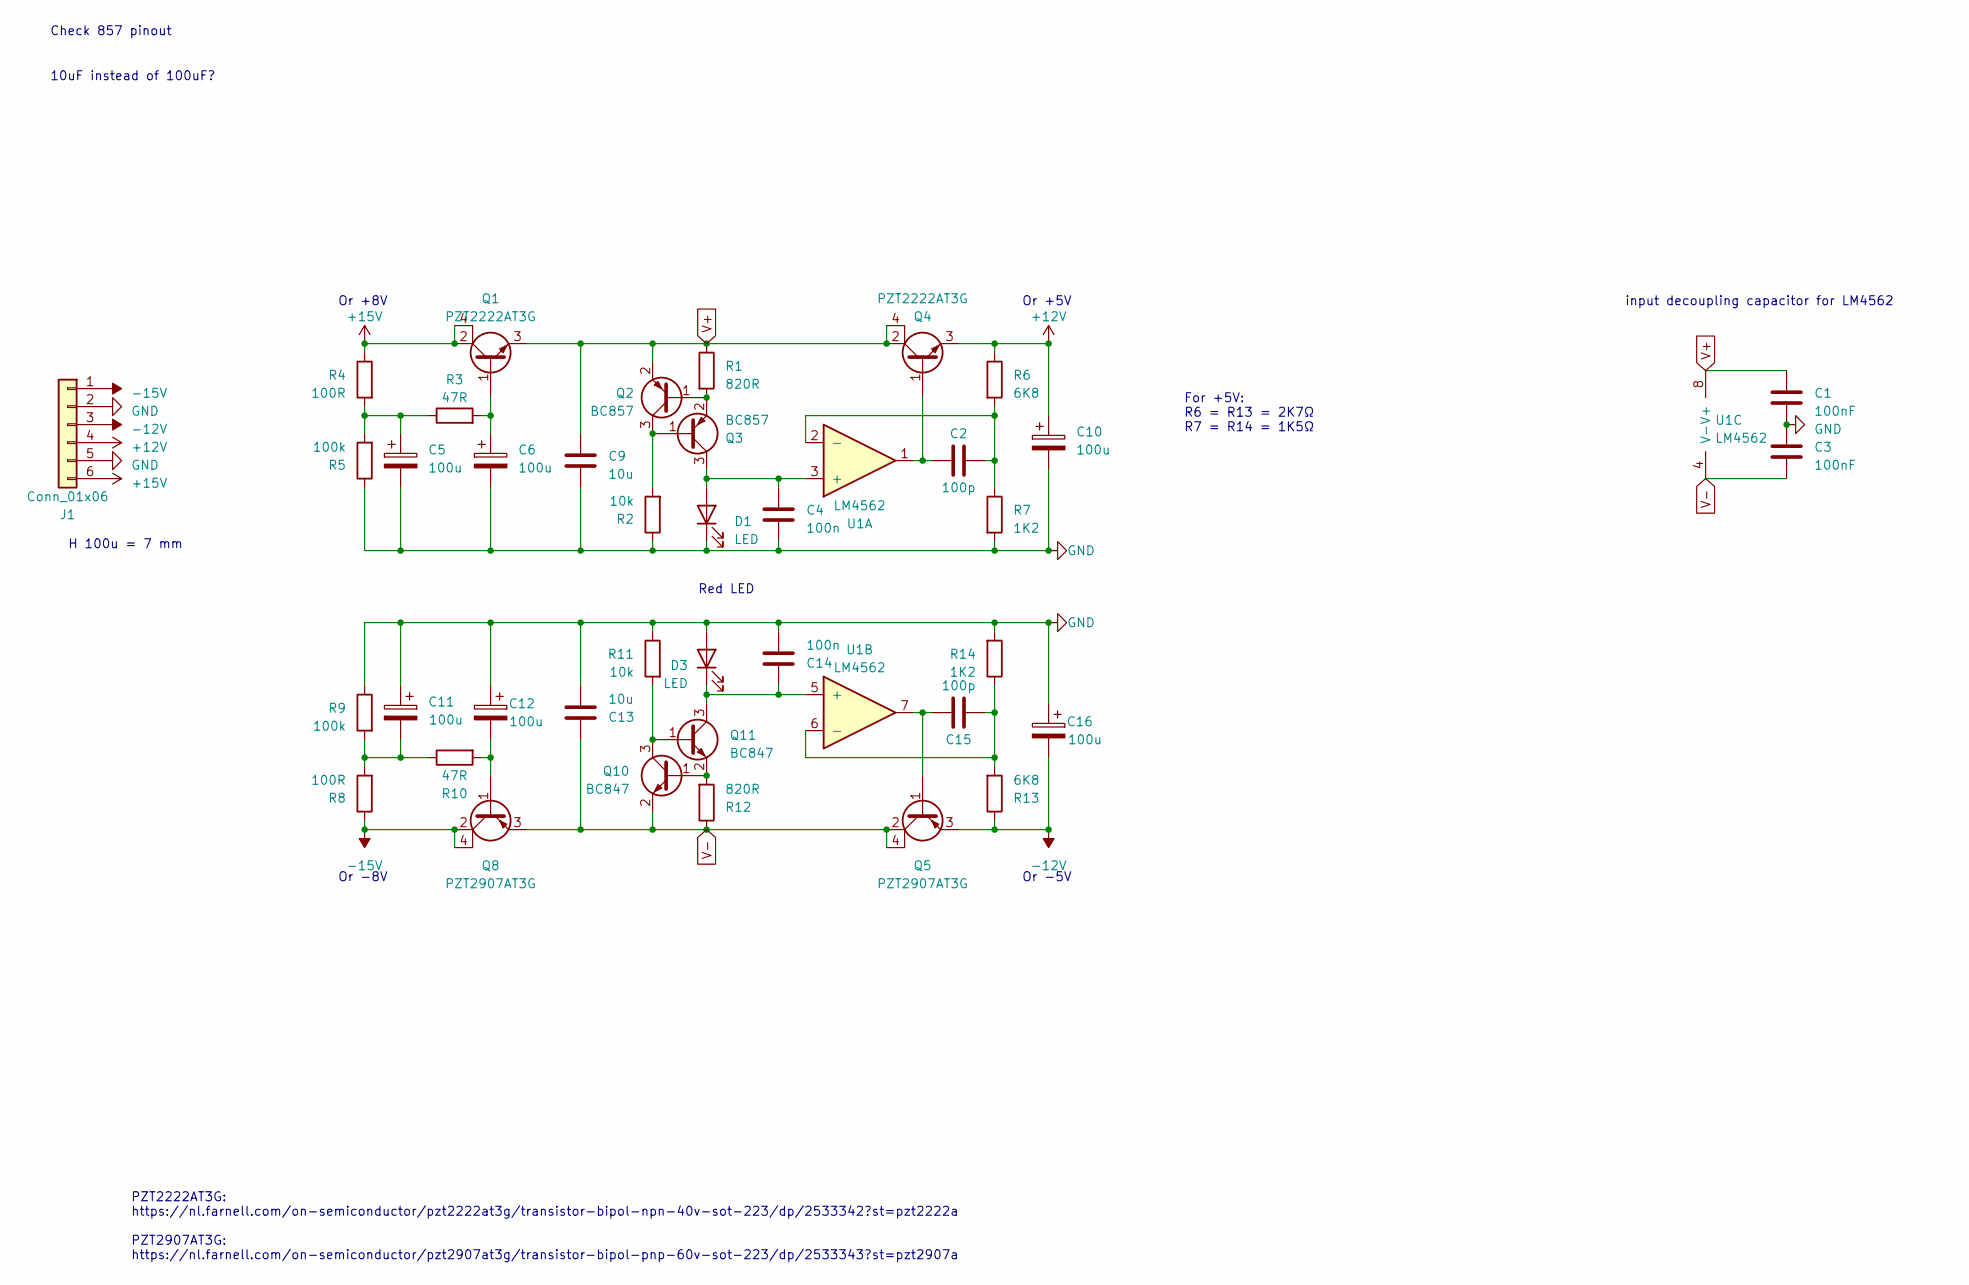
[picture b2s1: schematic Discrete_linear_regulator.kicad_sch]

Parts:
C1, C3: 100nF; C_0402_1005Metric
C2, C15: 100p; C_0402_1005Metric
C4, C14: 100n; C_0402_1005Metric
C5, C6, C10, C11, C12, C16: 100u; CP_Radial_D8.0mm_P3.50mm
C9, C13: 10u; C_1210_3225Metric
D1, D3: LED; LED_0805_2012Metric
J1: Conn_01x06; PinHeader_1x06_P2.54mm_Horizontal
Q1, Q4: PZT2222AT3G; SOT-223
Q2, Q3: BC857; SOT-23
Q5, Q8: PZT2907AT3G; SOT-223
Q10, Q11: BC847; SOT-23
R1, R12: 820R; R_0402_1005Metric
R2, R11: 10k; R_0402_1005Metric
R3, R10: 47R; R_0402_1005Metric
R4, R8: 100R; R_0402_1005Metric
R5, R9: 100k; R_0402_1005Metric
R6, R13: 6K8; R_0402_1005Metric
R7, R14: 1K2; R_0402_1005Metric
U1: LM4562; SOIC-8_3.9x4.9mm_P1.27mm

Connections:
+12V: C10.1, J1.4, Q4.3, R6.1
+15V: J1.6, Q1.2, Q1.4, R4.1
-12V: C16.2, J1.3, Q5.3, R13.1
-15V: J1.1, Q8.2, Q8.4, R8.1
GND: C1.2, C3.1, C4.2, C5.2, C6.2, C9.2, C10.2, C11.1, C12.1, C13.2, C14.2, C16.1, D1.1 (K), D3.2 (A), J1.2, J1.5, R2.1, R5.1, R7.2, R9.1, R11.1, R14.2
unnamed: C2.2, Q4.1, U1.1
unnamed: C5.1, R3.1, R4.2, R5.2
unnamed: C6.1, Q1.1, R3.2
unnamed: C11.2, R8.2, R9.2, R10.1
unnamed: C12.2, Q8.1, R10.2
unnamed: C15.2, Q5.1, U1.7
unnamed: C4.1, D1.2 (A), Q3.3 (C), U1.3 (+)
unnamed: C14.1, D3.1 (K), Q11.3 (C), U1.5 (+)
unnamed: Q2.1 (B), Q3.2 (E), R1.2
unnamed: Q2.3 (C), Q3.1 (B), R2.2
unnamed: Q10.1 (B), Q11.2 (E), R12.2
unnamed: Q10.3 (C), Q11.1 (B), R11.2
unnamed: C2.1, R6.2, R7.1, U1.2 (-)
unnamed: C15.1, R13.2, R14.1, U1.6 (-)
V+: C1.1, C9.1, Q1.3, Q2.2 (E), Q4.2, Q4.4, R1.1, U1.8 (V+)
V-: C3.2, C13.1, Q5.2, Q5.4, Q8.3, Q10.2 (E), R12.1, U1.4 (V-)

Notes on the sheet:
PZT2222AT3G: https://nl.farnell.com/on-semiconductor/pzt2222at3g/transistor-bipol-npn-40v-sot-223/dp/2533342?st=pzt2222a PZT2907AT3G: https://nl.farnell.com/on-semiconductor/pzt2907at3g/transistor-bipol-pnp-60v-sot-223/dp/2533343?st=pzt2907a
Or +5V
Check 857 pinout
Or -5V
For +5V: R6 = R13 = 2K7Ω R7 = R14 = 1K5Ω
Or -8V
input decoupling capacitor for LM4562
10uF instead of 100uF?
Or +8V
H 100u = 7 mm
Red LED

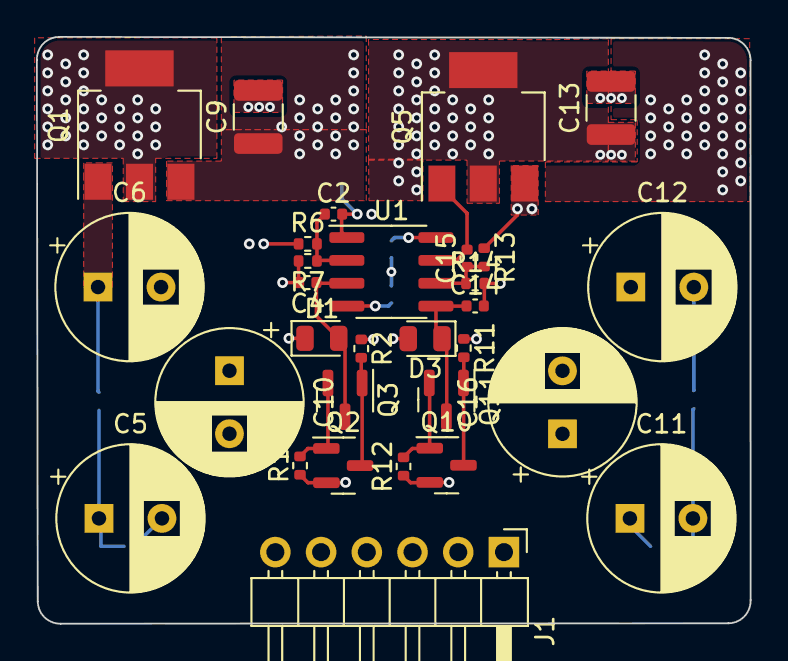
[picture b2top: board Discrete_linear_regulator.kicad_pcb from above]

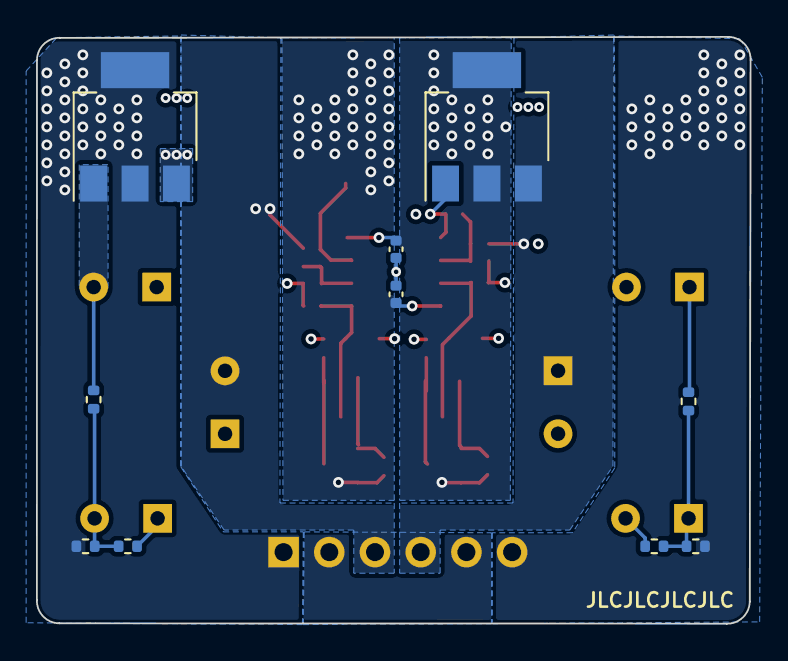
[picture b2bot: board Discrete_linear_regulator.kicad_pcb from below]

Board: 4 copper layers, 39.7 x 32.6 mm, 40 parts (10 on the bottom side), 21 nets.

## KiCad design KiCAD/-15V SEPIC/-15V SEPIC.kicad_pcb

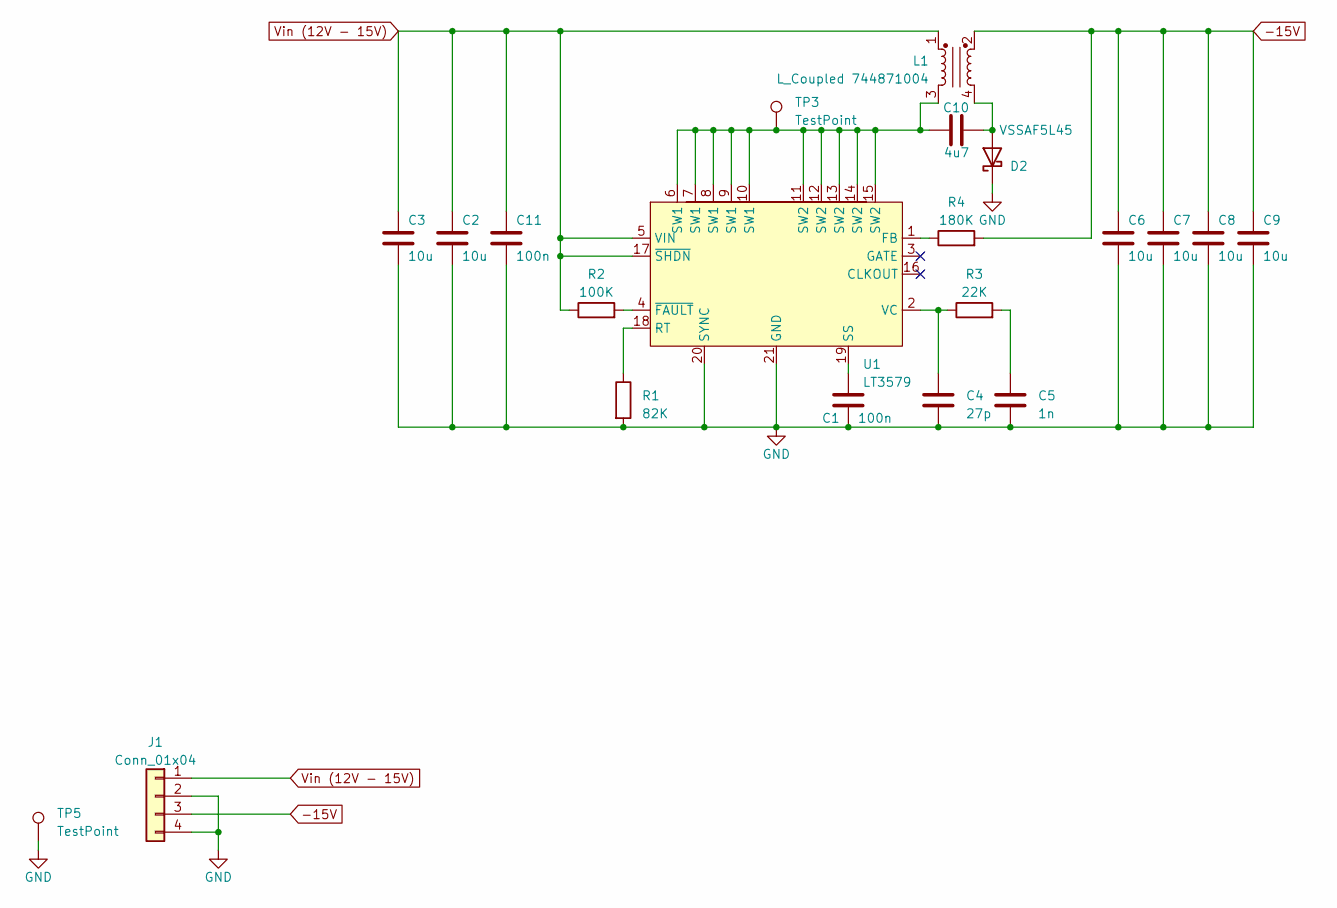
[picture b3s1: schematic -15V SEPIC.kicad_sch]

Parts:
C1, C11: 100n; C_0402_1005Metric
C2, C3, C6, C7, C8, C9: 10u; C_1210_3225Metric
C4: 27p; C_0402_1005Metric
C5: 1n; C_0402_1005Metric
C10: 4u7; C_1210_3225Metric
D2: VSSAF5L45; DO-221AC
J1: Conn_01x04; PinHeader_1x04_P2.54mm_Horizontal
L1: L_Coupled 744871004; L_Wuerth_WE-DD-Typ-L-Typ-XL-Typ-XXL
R1: 82K; R_0402_1005Metric
R2: 100K; R_0402_1005Metric
R3: 22K; R_0402_1005Metric
R4: 180K; R_0402_1005Metric
TP3, TP5: TestPoint; TestPoint_Pad_D1.0mm
U1: LT3579; TSSOP-20-1EP_4.4x6.5mm_P0.65mm_EP2.75x3.85mm

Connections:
-15V: C6.1, C7.1, C8.1, C9.1, J1.3, L1.2, R4.2
GND: C1.2, C2.2, C3.2, C4.2, C5.2, C6.2, C7.2, C8.2, C9.2, C11.2, D2.1 (K), J1.2, J1.4, R1.2, TP5.1, U1.20 (SYNC), U1.21 (GND)
unnamed: C5.1, R3.2
unnamed: C10.1, L1.3, TP3.1, U1.6 (SW1), U1.7 (SW1), U1.8 (SW1), U1.9 (SW1), U1.10 (SW1), U1.11 (SW2), U1.12 (SW2), U1.13 (SW2), U1.14 (SW2), U1.15 (SW2)
unnamed: C10.2, D2.2 (A), L1.4
unnamed: R4.1, U1.1 (FB)
unnamed: R1.1, U1.18 (RT)
unnamed: C1.1, U1.19 (SS)
unnamed: C4.1, R3.1, U1.2 (VC)
unnamed: R2.2, U1.4 (~FAULT)
Vin (12V - 15V): C2.1, C3.1, C11.1, J1.1, L1.1, R2.1, U1.5 (VIN), U1.17 (~SHDN)

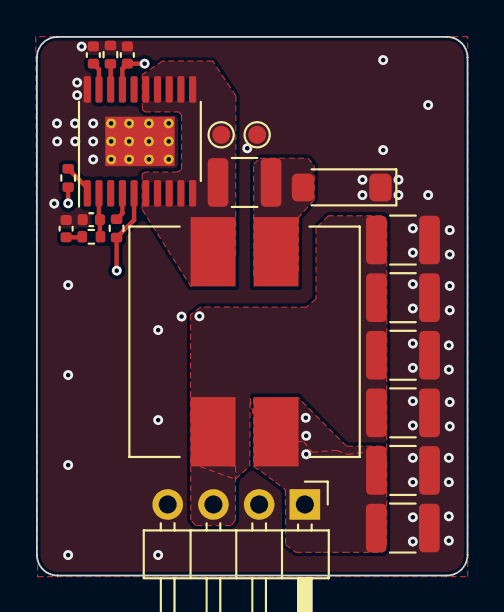
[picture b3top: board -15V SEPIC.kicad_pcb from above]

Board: 4 copper layers, 23.9 x 29.9 mm, 21 parts (0 on the bottom side), 11 nets.
